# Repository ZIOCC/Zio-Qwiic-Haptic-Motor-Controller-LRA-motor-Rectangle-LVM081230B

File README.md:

# Zio Qwiic Haptic Motor Controller + LRA Motor Z-Axis (Rectangle-LVM081230B)

> This product can be available for purchase [here](https://www.smart-prototyping.com/Zio-Qwiic-Haptic-Motor-Controller-LRA-motor-z-axis-LVM081230B).

#### Description

As the product name itself says, this tiny board combines the Haptic motor driver (DRV2605L) and the rectangle LRA motor. So they can work together directly. 

The rectangle LRA motor on board, compares to the round LRA motor, the vibrations are directed in only the Z-axis. This offers users a greater choice in design as they can produce vibrations in either horizontal or vertical directions.

Check the source documentation [here](https://www.precisionmicrodrives.com/vibration-motors/linear-resonant-actuators-lras/)

It is a Qwiic (I2C) compatible model, with the qwiic system you can embed this motor board into Qwiic project without soldering and jumper wire connection!

#### Specification

* Motor driver IC: DRV2605L
* Z-Axis motor Manufacture Number: LVM081230B
* IC: DRV2605L
* I2C address: 0x5A
* PCB Dimension: 14.5 x 35.7 mm
* Weight: 4.9g

#### Links

* [PCB source file](https://github.com/ZIOCC/Zio-Qwiic-Haptic-Motor-Controller-LRA-motor-Z-axis-LVM081230B/tree/master/EAGLE)
* [PCB Schematic](https://github.com/ZIOCC/Zio-Qwiic-Haptic-Motor-Controller-LRA-motor-Z-axis-LVM081230B/blob/master/Haptic%20Motor%20driver%20board%20%2B%20LRA%20z-axis%20LVM081230B.pdf)
* [DRV2605L Datasheet](https://www.smart-prototyping.com/image/data/2_components/sensors/101802DRV2605L%20Haptic%20Driver/DRV2605.pdf)
* [Demo Code (adafruit DRV2605 Library)](https://github.com/adafruit/Adafruit_DRV2605_Library)

###### About Zio
> Zio is a new line of open sourced, compact, and grid layout boards, fully integrated for Arduino and Qwiic ecosystem. Designed ideally for wearables, robotics, small-space limitations or other on the go projects. Check out other awesome Zio products [here](https://www.smart-prototyping.com/Zio).

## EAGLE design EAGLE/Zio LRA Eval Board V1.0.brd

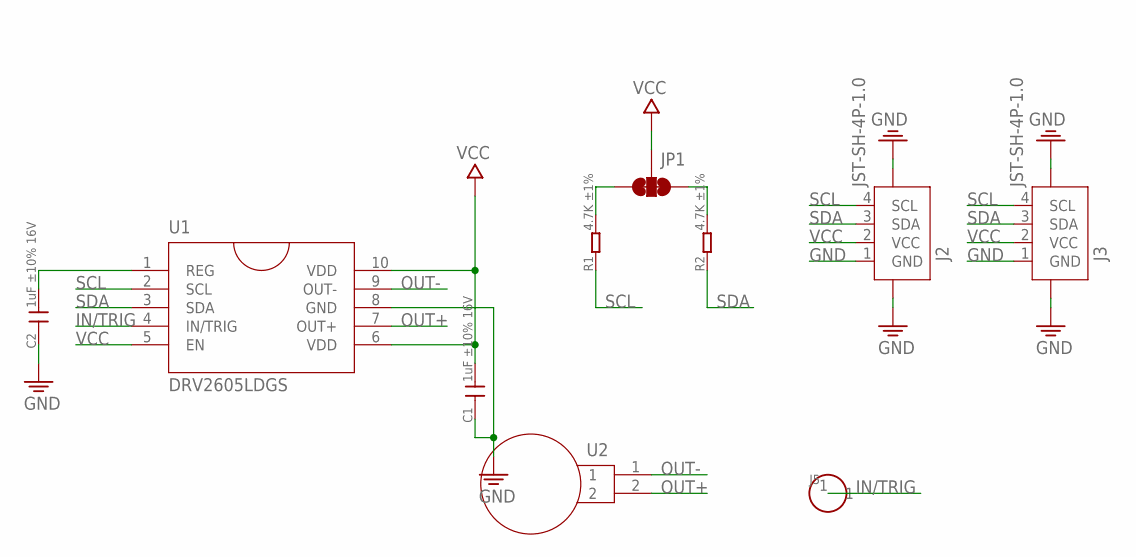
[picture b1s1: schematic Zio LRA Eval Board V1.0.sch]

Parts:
C1, C2: 1uF ±10% 16V; C0603
J2, J3: JST-SH-4P-1.0; JST-SH-4P
J5: HEADER-1P; 1P-40MIL
JP1: SMT-JUMPER_3_2-NC_TRACE
R1, R2: 4.7K ±1%; R0402
U1: DRV2605LDGS; VSSOP10
U2: LRA-MOTOR-081230B

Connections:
GND: C1.1, C2.1, J2.1 (GND), J2.NC1 (5), J2.NC2 (6), J3.1 (GND), J3.NC1 (5), J3.NC2 (6), U1.8 (GND)
IN/TRIG: J5.1, U1.4 (IN/TRIG)
unnamed: C2.2, U1.1 (REG)
unnamed: JP1.3, R1.2
unnamed: JP1.1, R2.2
OUT+: U1.7 (OUT+), U2.2
OUT-: U1.9 (OUT-), U2.1
SCL: J2.4 (SCL), J3.4 (SCL), R1.1, U1.2 (SCL)
SDA: J2.3 (SDA), J3.3 (SDA), R2.1, U1.3 (SDA)
VCC: C1.2, J2.2 (VCC), J3.2 (VCC), JP1.2, U1.5 (EN), U1.6 (VDD), U1.10 (VDD)

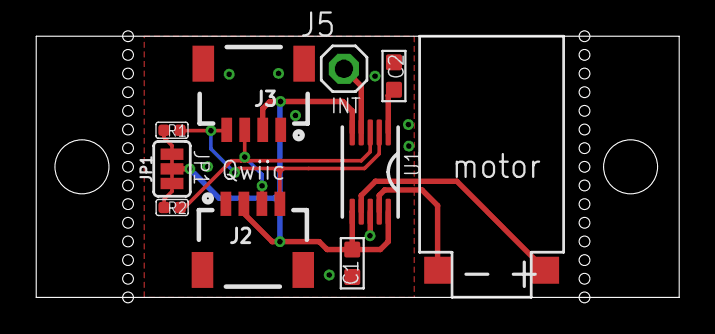
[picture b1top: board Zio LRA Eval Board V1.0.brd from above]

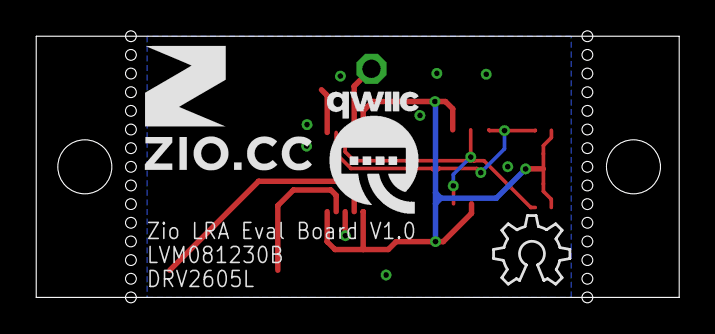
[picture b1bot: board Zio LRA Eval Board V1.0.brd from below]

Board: 2 copper layers, 35.7 x 14.5 mm, 13 parts (3 on the bottom side), 10 nets.

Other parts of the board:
U$1: 7MM
U$2: OSHW_6X150_NOTEXT
U$5: QWIIC-LOGO-MEDIUM
